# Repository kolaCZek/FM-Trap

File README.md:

# FM Trap

[OSHPark Project](https://oshpark.com/shared_projects/sTO339dT)

## Characteristics

## BOM

 - 2x [1008 33nH](https://www.tme.eu/en/details/cw1008-33/smd-coils/ferrocore/)
 - 2x [1008 180nH](https://www.tme.eu/en/details/cw1008-180/smd-coils/ferrocore/)
 - 1x [1008 56nH](https://www.tme.eu/en/details/cw1008-56/smd-coils/ferrocore/)
 - 2x [0805 82pF](https://www.tme.eu/en/details/cc0805jrnpo9820/0805-mlcc-smd-capacitors/yageo/cc0805jrnpo9bn820/)
 - 2x [0805 15pF](https://www.tme.eu/en/details/cc0805jrnpo9150/0805-mlcc-smd-capacitors/yageo/cc0805jrnpo9bn150/)
 - 1x [0805 47pF](https://www.tme.eu/en/details/cc0805jrnpo9470/0805-mlcc-smd-capacitors/yageo/cc0805jrnpo9bn470/)
 - 2x [SMA](https://www.ebay.com/sch/i.html?_from=R40&_sacat=0&_nkw=sma+female+pcb+edge+mount&rt=nc&LH_BIN=1)
 - 1x [PCB](https://oshpark.com/shared_projects/sTO339dT)

## Other Projects

 - [2m Band Pass Filter](https://github.com/kolaCZek/2m-Band-Pass-Filter)
 - [2m/70cm Diplexer](https://github.com/kolaCZek/2m-70cm-Diplexer)
 - [Bias-T](https://github.com/kolaCZek/Bias-T)

## License

[Apache License Version 2.0](./LICENSE)

## Donate

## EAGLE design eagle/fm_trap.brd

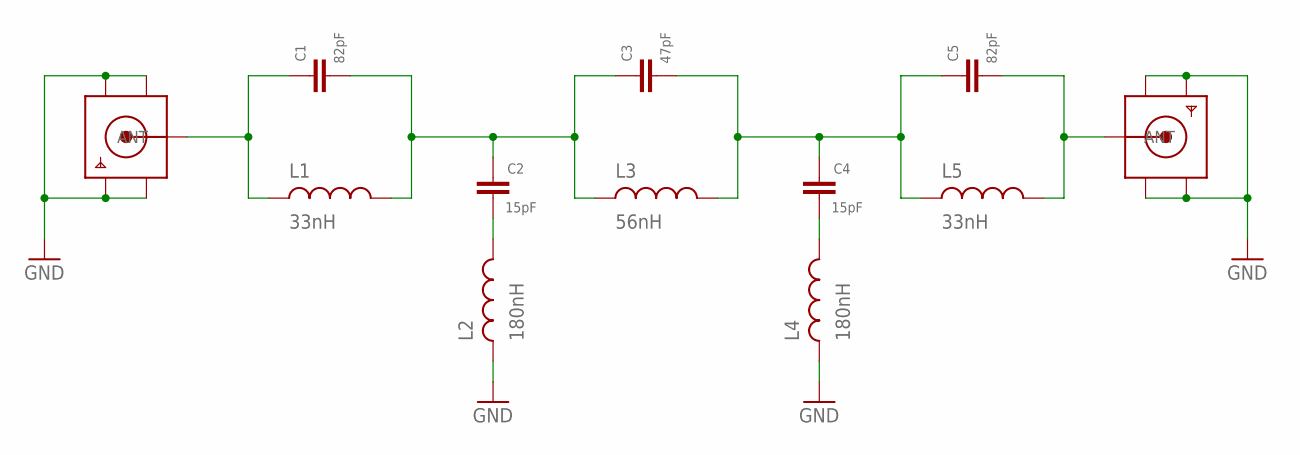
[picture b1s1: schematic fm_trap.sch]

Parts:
C1, C5: 82pF; 0805
C2, C4: 15pF; 0805
C3: 47pF; 0805
L1, L5: 33nH; 1008INDUCTOR
L2, L4: 180nH; 1008INDUCTOR
L3: 56nH; 1008INDUCTOR
X1, X2: SMACONNECTOR_EDGE; SMA_EDGELAUNCH

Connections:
GND: L2.P$1, L4.P$1, X1.GND@1 (GND4), X1.GND@2 (GND3), X1.GND@3 (GND2), X1.GND@4 (GND1), X2.GND@1 (GND4), X2.GND@2 (GND3), X2.GND@3 (GND2), X2.GND@4 (GND1)
unnamed: C1.P$1, C2.P$2, C3.P$2, L1.P$2, L3.P$1
unnamed: C5.P$1, L5.P$2, X2.P (ANT)
unnamed: C2.P$1, L2.P$2
unnamed: C1.P$2, L1.P$1, X1.P (ANT)
unnamed: C3.P$1, C4.P$2, C5.P$2, L3.P$2, L5.P$1
unnamed: C4.P$1, L4.P$2

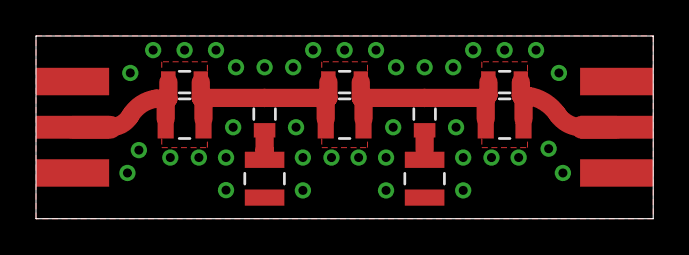
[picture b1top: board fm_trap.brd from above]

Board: 2 copper layers, 34.3 x 10.2 mm, 12 parts (0 on the bottom side), 7 nets.

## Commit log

2018-02-15 init commit
2018-02-15 Readme - Other projects
2022-01-25 Add Buy me coffe button
